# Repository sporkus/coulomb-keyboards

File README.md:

# Coulomb keyboards

12-column EC keyboards

Status: WIP

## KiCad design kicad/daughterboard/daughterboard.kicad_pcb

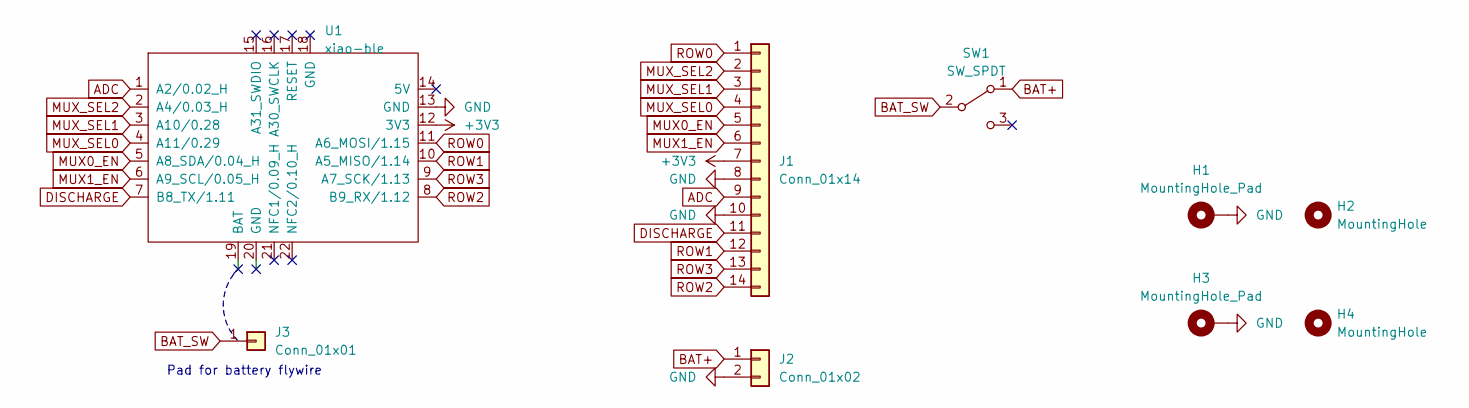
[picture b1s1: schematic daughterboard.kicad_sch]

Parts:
H1, H3: MountingHole_Pad; MountingHole_2.2mm_M2_Pad
H2, H4: MountingHole; MountingHole_2.2mm_M2_DIN965
J1: Conn_01x14; Hirose_FH12-14S-0.5SH_1x14-1MP_P0.50mm_Horizontal
J2: Conn_01x02; JST_PH_S2B-PH-K_1x02_P2.00mm_Horizontal
J3: Conn_01x01; PinHeader_1x01_P2.54mm_Vertical
SW1: SW_SPDT; switch-MSK-12C02-smd
U1: xiao-ble; xiao-ble-smd-reverse

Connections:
+3V3: J1.7, U1.12 (3V3)
ADC: J1.9, U1.1 (A2/0.02_H)
BAT+: J2.1, SW1.1 (A)
BAT_SW: J3.1, SW1.2 (B)
DISCHARGE: J1.11, U1.7 (B8_TX/1.11)
GND: H1.1, H3.1, J1.8, J1.10, J2.2, U1.13 (GND)
MUX0_EN: J1.5, U1.5 (A8_SDA/0.04_H)
MUX1_EN: J1.6, U1.6 (A9_SCL/0.05_H)
MUX_SEL0: J1.4, U1.4 (A11/0.29)
MUX_SEL1: J1.3, U1.3 (A10/0.28)
MUX_SEL2: J1.2, U1.2 (A4/0.03_H)
ROW0: J1.1, U1.11 (A6_MOSI/1.15)
ROW1: J1.12, U1.10 (A5_MISO/1.14)
ROW2: J1.14, U1.8 (B9_RX/1.12)
ROW3: J1.13, U1.9 (A7_SCK/1.13)

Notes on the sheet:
Pad for battery flywire

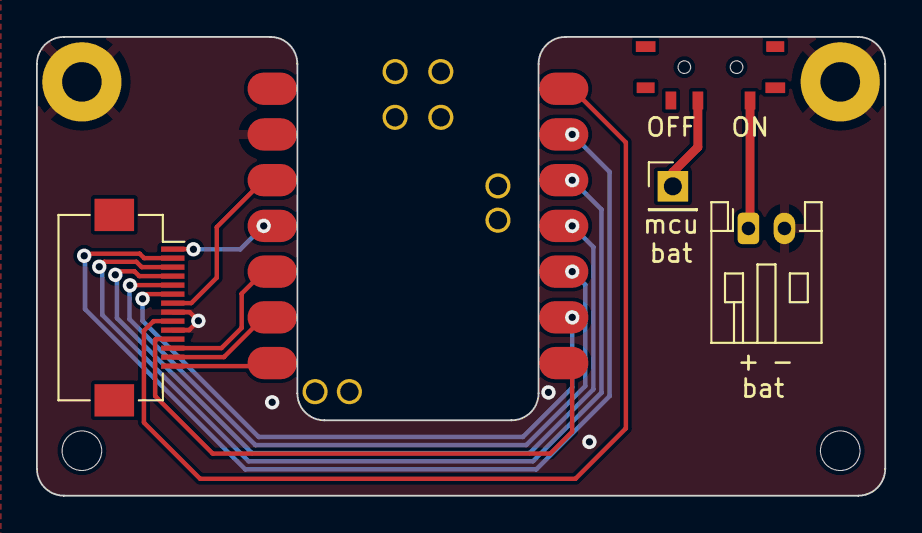
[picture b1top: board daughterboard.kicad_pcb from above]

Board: 2 copper layers, 47.1 x 25.5 mm, 9 parts (0 on the bottom side), 15 nets.

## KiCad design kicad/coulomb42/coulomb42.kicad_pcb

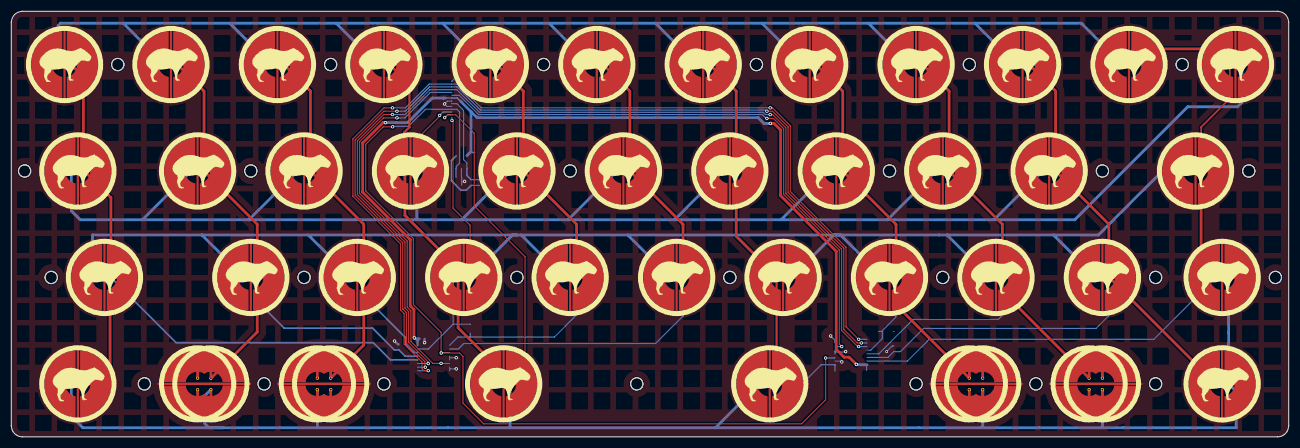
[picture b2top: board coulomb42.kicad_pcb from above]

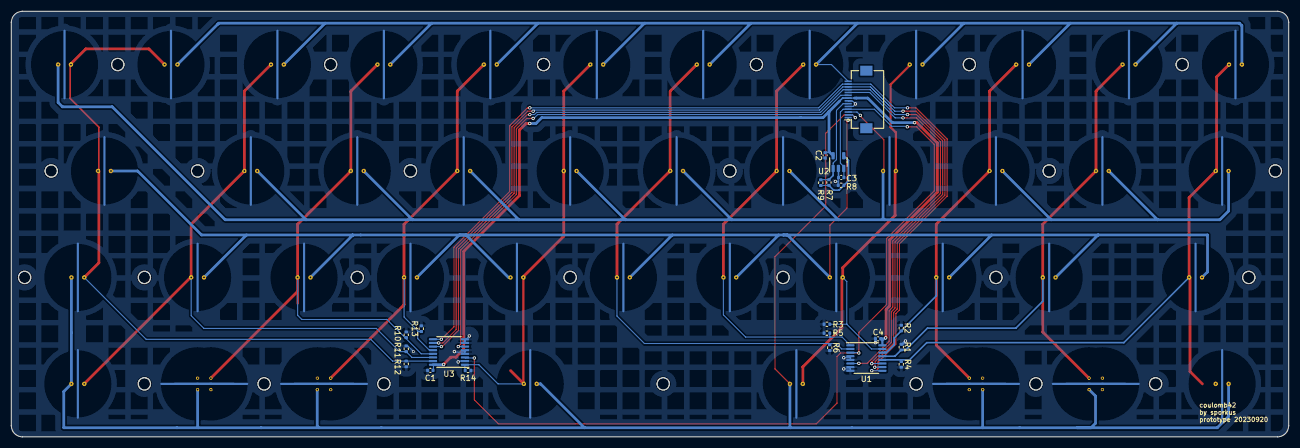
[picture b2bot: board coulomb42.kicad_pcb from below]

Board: 2 copper layers, 228.6 x 76.1 mm, 90 parts (22 on the bottom side), 25 nets.

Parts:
C1, C2, C4: 100n; C_0402_1005Metric
C3: 220pF; C_0402_1005Metric
ECSW1, ECSW2, ECSW3, ECSW4, ECSW5, ECSW6, ECSW7, ECSW8, ECSW9, ECSW10, ECSW11, ECSW12, ECSW13, ECSW14, ECSW15, ECSW16, ECSW17, ECSW18, ECSW19, ECSW20, ECSW21, ECSW22, ECSW23, ECSW24, ECSW25, ECSW26, ECSW27, ECSW28, ECSW29, ECSW30, ECSW31, ECSW32, ECSW33, ECSW34, ECSW35, ECSW42: capy_pad_1U
ECSW36, ECSW37, ECSW40, ECSW41: ecs_pad_combo_0.125u_offset
ECSW38, ECSW39: capy_pad_2U
H1, H2, H3, H4, H5, H6, H7, H8, H9, H10, H11, H12, H13, H14, H15, H16, H17, H18, H19, H20, H21, H22, H23, H24, H25, H26: MountingHole; MountingHole_2.2mm_M2
J1: Conn_01x14; Hirose_FH12-14S-0.5SH_1x14-1MP_P0.50mm_Horizontal
R1, R2, R3, R4, R5, R6, R7, R10, R11, R12, R13, R14: 100k; R_0402_1005Metric
R8: 1k; R_0402_1005Metric
R9: DNP; R_0402_1005Metric
U1, U3: 74HC4051; TSSOP-16_4.4x5mm_P0.65mm
U2: OPA354; SOT-23-5

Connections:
+3V3: C1.2, C2.2, C4.2, J1.8, U1.16 (VCC), U2.5 (V+), U3.16 (VCC)
ADC: J1.6, R7.1, R9.1, U2.1
COL0: ECSW1.1, ECSW13.1, ECSW24.1, ECSW35.1, R4.1, U1.12 (A3)
COL1: ECSW2.1, ECSW14.1, ECSW25.1, ECSW36.1, R1.1, U1.13 (A0)
COL2: ECSW3.1, ECSW15.1, ECSW26.1, ECSW37.1, R2.1, U1.14 (A1)
COL3: ECSW4.1, ECSW16.2, ECSW27.2, ECSW38.2, R3.1, U1.15 (A2)
COL4: ECSW5.1, ECSW17.1, ECSW28.1, R5.1, U1.1 (A4)
COL5: ECSW6.1, ECSW18.1, ECSW29.1, R6.1, U1.2 (A6)
COL6: ECSW7.1, ECSW19.1, ECSW30.2, ECSW39.1, R14.1, U3.1 (A4)
COL7: ECSW8.1, ECSW20.1, ECSW31.1, ECSW40.1, R13.1, U3.12 (A3)
COL8: ECSW9.1, ECSW21.1, ECSW32.1, ECSW41.1, R10.1, U3.13 (A0)
COL9: ECSW10.1, ECSW22.1, ECSW33.1, ECSW42.2, R11.1, U3.14 (A1)
COL10: ECSW11.1, ECSW12.2, ECSW23.1, ECSW34.2, R12.1, U3.15 (A2)
GND: C1.1, C2.1, C3.2, C4.1, ECSW1.3, ECSW2.3, ECSW3.3, ECSW4.3, ECSW5.3, ECSW6.3, ECSW7.3, ECSW8.3, ECSW9.3, ECSW10.3, ECSW11.3, ECSW12.3, ECSW13.3, ECSW14.3, ECSW15.3, ECSW16.3, ECSW17.3, ECSW18.3, ECSW19.3, ECSW20.3, ECSW21.3, ECSW22.3, ECSW23.3, ECSW24.3, ECSW25.3, ECSW26.3, ECSW27.3, ECSW28.3, ECSW29.3, ECSW30.3, ECSW31.3, ECSW32.3, ECSW33.3, ECSW34.3, ECSW35.3, ECSW36.3, ECSW37.3, ECSW38.3, ECSW39.3, ECSW40.3, ECSW41.3, ECSW42.3, J1.5, J1.7, R1.2, R2.2, R3.2, R4.2, R5.2, R6.2, R8.2, R10.2, R11.2, R12.2, R13.2, R14.2, U1.4 (A7), U1.5 (A5), U1.7 (VEE), U1.8 (GND), U2.2 (V-), U3.2 (A6), U3.4 (A7), U3.5 (A5), U3.7 (VEE), U3.8 (GND)
MUX0_EN: J1.10, U1.6 (~E)
MUX1_EN: J1.9, U3.6 (~E)
MUX_COMMON: C3.1, J1.4, U1.3 (A), U2.3 (+), U3.3 (A)
MUX_SEL0: J1.11, U1.11 (S0), U3.11 (S0)
MUX_SEL1: J1.12, U1.10 (S1), U3.10 (S1)
MUX_SEL2: J1.13, U1.9 (S2), U3.9 (S2)
unnamed: R7.2, R8.1, R9.2, U2.4 (-)
ROW0: ECSW1.2, ECSW2.2, ECSW3.2, ECSW4.2, ECSW5.2, ECSW6.2, ECSW7.2, ECSW8.2, ECSW9.2, ECSW10.2, ECSW11.2, J1.14
ROW1: ECSW12.1, ECSW13.2, ECSW14.2, ECSW15.2, ECSW16.1, ECSW17.2, ECSW18.2, ECSW19.2, ECSW20.2, ECSW21.2, ECSW22.2, J1.3
ROW2: ECSW23.2, ECSW24.2, ECSW25.2, ECSW26.2, ECSW27.1, ECSW28.2, ECSW29.2, ECSW30.1, ECSW31.2, ECSW32.2, ECSW33.2, J1.1
ROW3: ECSW34.1, ECSW35.2, ECSW36.2, ECSW37.2, ECSW38.1, ECSW39.2, ECSW40.2, ECSW41.2, ECSW42.1, J1.2

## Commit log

2023-09-20 init
